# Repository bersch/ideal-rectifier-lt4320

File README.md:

Active Rectifier with LT4320
============================

The KiCad files.

Schematics: https://github.com/bersch/ideal-rectifier-lt4320/blob/master/ideal-rectifier-lt4320.pdf

4LayerPCB: https://github.com/bersch/ideal-rectifier-lt4320/blob/master/pcb.png

For more information please refer to 

- http://www.linear.com/product/LT4320

* http://cds.linear.com/docs/en/datasheet/4320fb.pdf

- http://cds.linear.com/docs/en/design-note/dn519f.pdf

- http://cds.linear.com/docs/en/demo-board-manual/dc1823afa.pdf

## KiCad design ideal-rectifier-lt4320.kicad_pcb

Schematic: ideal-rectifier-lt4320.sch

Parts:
C1, C2, C3, C4: 2.2µ; C1206
D1: D_Shottky; Diode-SMB
JP1, JP2: ~~; FASTON-6.3mm-45deg_P
JP3: +; FASTON-6.3mm-45deg_P
JP4: -; FASTON-6.3mm-45deg_P
T1, T2, T3, T4: BSC028; PG-TDSON-8_P
U1: LT4320; MSE-12

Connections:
/ctr1: T2.1, U1.11
/ctr2: T4.1, U1.2
/ctr3: T1.1, U1.5
/ctr4: T3.1, U1.6
/th_ac1: JP1.1, T1.3, T2.2, U1.12
/th_ac2: JP2.1, T3.3, T4.2, U1.1
/th_plus: C1.1, C2.1, C3.1, C4.1, D1.1, JP3.1, T2.3, T4.3, U1.9
GND: C1.2, C2.2, C3.2, C4.2, D1.2, JP4.1, T1.2, T3.2, U1.7

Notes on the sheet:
Title: Active Rectifier with LT4320 v1.0 2018-01-07 Author: Bernhard Schneider <bernhard@neaptide.org> License: CERN Open Hardware Licence v1.2
T1-T4 ====== @60V BSC028 RDS = 2.8 mOhm, VGS = 1.2V @72V SIR826 RDS = 6.5 mOhm, VGS = 1.2V
JP1-JP4: FASTON-6.3mm-45deg

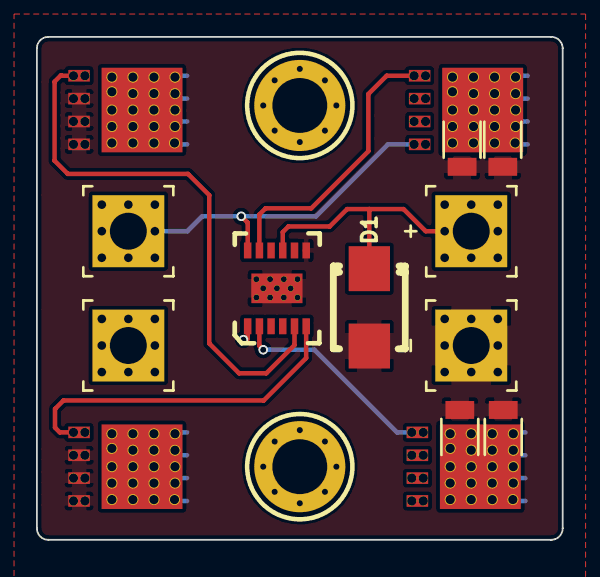
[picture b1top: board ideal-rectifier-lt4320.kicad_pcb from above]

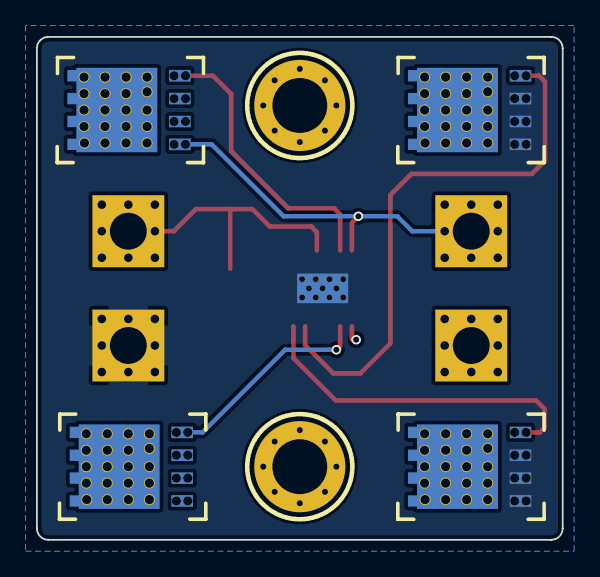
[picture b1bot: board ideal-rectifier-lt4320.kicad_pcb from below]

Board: 4 copper layers, 29.2 x 27.9 mm, 16 parts (4 on the bottom side), 8 nets.

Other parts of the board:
P11, P14: CONN_01X01; 1pin-my

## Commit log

2016-06-15 Create README.md
    Project Notes
2016-06-16 minor
2018-01-07 v1.0
